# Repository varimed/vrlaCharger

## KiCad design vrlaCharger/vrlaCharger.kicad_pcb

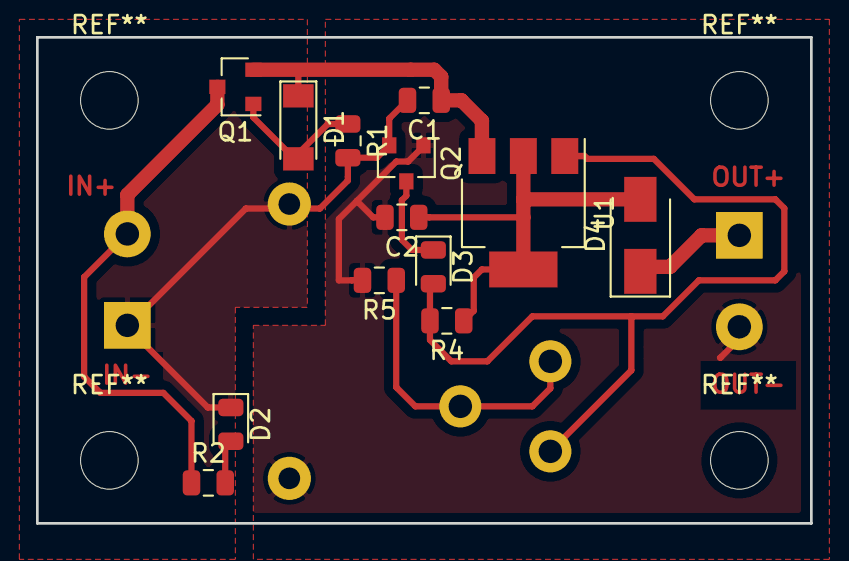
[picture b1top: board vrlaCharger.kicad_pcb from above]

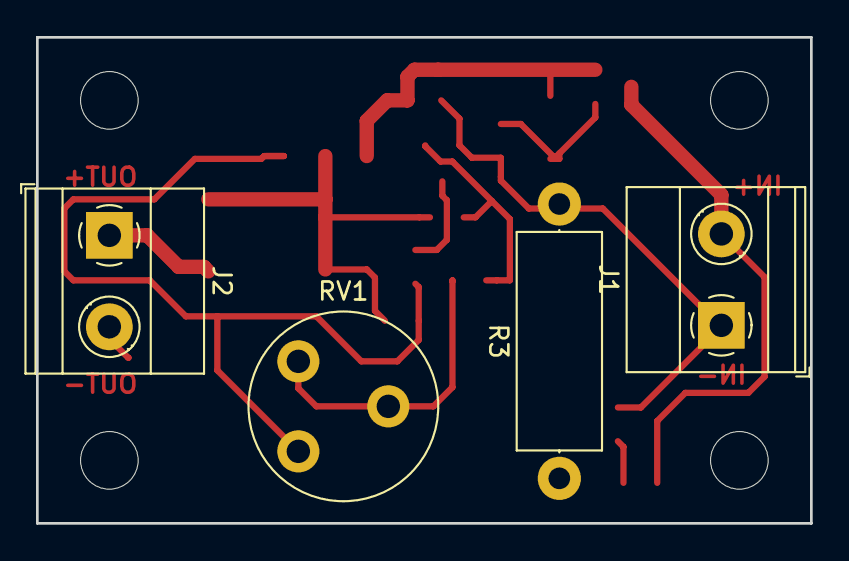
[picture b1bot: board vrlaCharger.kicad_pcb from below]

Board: 2 copper layers, 43.0 x 27.0 mm, 17 parts (4 on the bottom side), 11 nets.

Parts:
C1, C2: 100n; C_0805_2012Metric
D1: 10V; D_MiniMELF
D2, D3: LED; D_0805_2012Metric
D4: D_Schottky; D_SMA
J1, J2: Conn_01x02; TerminalBlock_Phoenix_MKDS-1,5-2-5.08_1x02_P5.08mm_Horizont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
Q1: Q_PMOS_GSD; SOT-23
Q2: Q_NPN_BEC; SOT-23
R1: 10k; R_0805_2012Metric
R2: 1k; R_0805_2012Metric
R3: 1R; R_Axial_DIN0414_L11.9mm_D4.5mm_P15.24mm_Horizontal
R4: 470R; R_0805_2012Metric
R5: 2k2; R_0805_2012Metric
RV1: 10k; Potentiometer_Piher_PT-10-V05_Vertical
U1: LM317_3PinPackage; SOT-223-3_TabPin2

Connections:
unnamed: C1.1, D1.1, Q1.2, U1.3
unnamed: C1.2, D2.1, J1.1, Q2.2, R1.2, R3.2
unnamed: C2.1, D4.2, R4.1, U1.2
unnamed: C2.2, J2.2, Q2.1, R3.1, R5.2
unnamed: D1.2, Q1.1, R1.1
unnamed: D2.2, R2.2
unnamed: D3.1, Q2.3
unnamed: D3.2, R4.2, RV1.1, U1.1
unnamed: D4.1, J2.1
unnamed: J1.2, Q1.3, R2.1
unnamed: R5.1, RV1.2, RV1.3

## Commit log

2019-09-14 Schematic and PCB draft
2019-09-16 THT elements flipped to other side
2019-10-17 Minor changes and production files, .gitignore updated
